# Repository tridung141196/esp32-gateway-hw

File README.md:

# esp32-gateway-hw

## Features

esp32-gateway-hw có thể:
- Điện áp ngõ vào 4 đến 40VDC.

- Sử dụng được nguồn DC, USB, Pin ( có chức năng tự sạc).

- Theo dõi vị trí và trả về thông tin cho người dùng thông qua module GPS Neo6m và module GSM Sim800c.

- Hệ thống đèn báo nguồn , GPS , GSM.

# Nguyên lý hoạt động

- SHield sử dụng module GPS neo6m để định vị tọa độ của thiết bị thông qua hệ thống định vị toàn cầu (GPS) sau đó gửi thông tin toạ độ thiết bị đến người dùng thông qua module sim800c

## Hardware

### Các module đi kèm

ESP32-WROVER-V3

GSM SIM800C

GPS NEO6M

### Schematics

### PCB Layout

### 3D

### Gerber

//[Download](./assets/esp32-cam-shield.zip)

### BOM 

| Designator | Package | Quantity | Designation  |
|---------------------|--------------------------------|----------|-------------------------|
|		      |		                       |	  |	                    |
### Remark

This project was in development phase - we will remove this remark after release

# License

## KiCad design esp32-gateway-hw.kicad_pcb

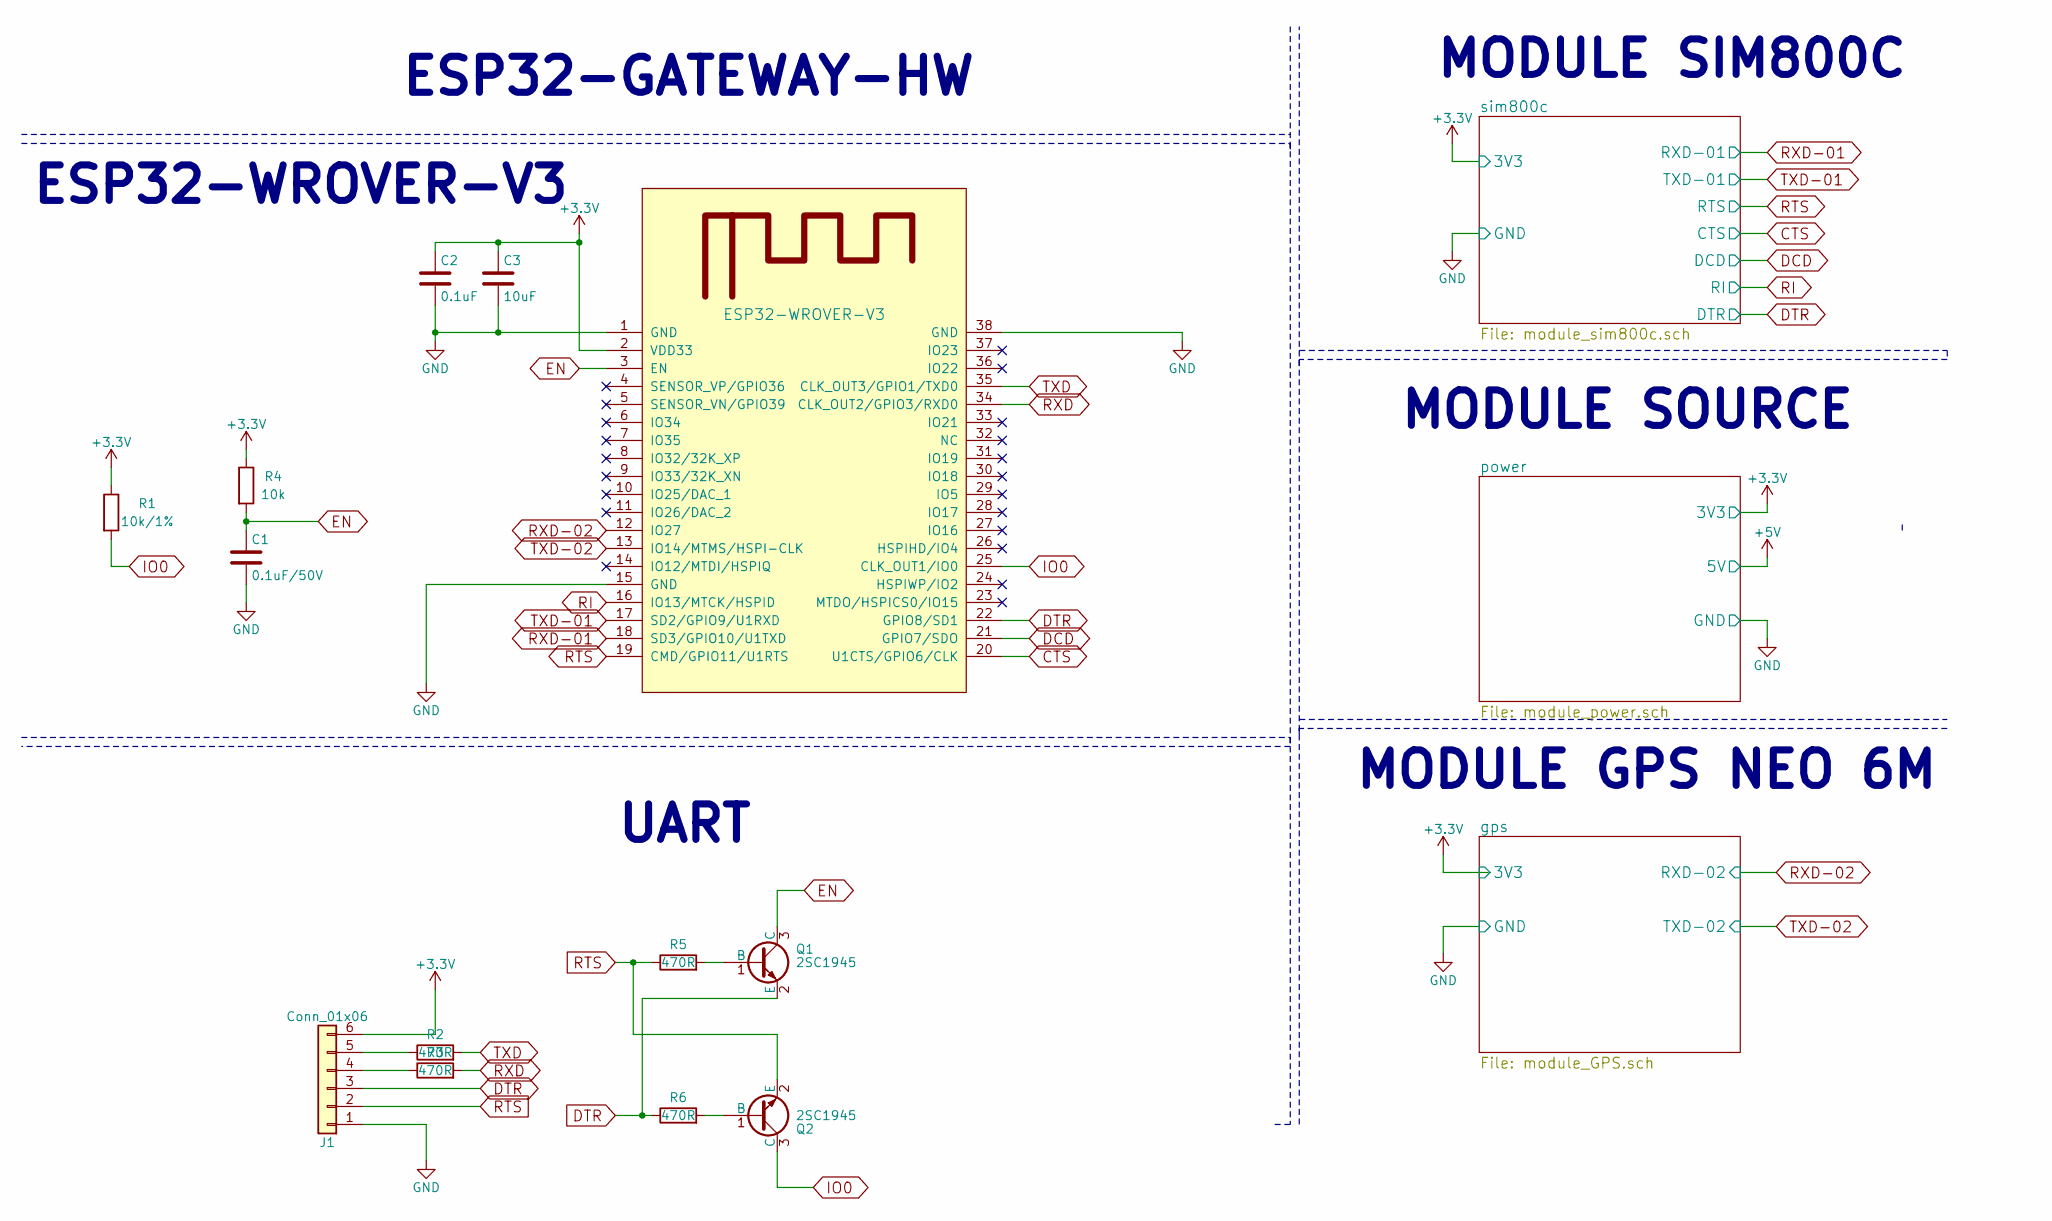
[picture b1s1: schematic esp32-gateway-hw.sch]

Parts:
C1: 0.1uF/50V; C_0603
C2: 0.1uF; C_0603
C3: 10uF; C_0603
J1: Conn_01x06; Pin_Header_Straight_1x06_Pitch2.54mm
Q1, Q2: 2SC1945; SOT-23
R1: 10k/1%; R_0603
R2, R3, R5, R6: 470R; R_0603
R4: 10k; R_0603
U1: ESP32-WROVER-V3; esp32-wrover-32S

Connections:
+3V3: C2.1, C3.1, J1.6, R1.1, R4.1, U1.2 (VDD33); also elsewhere on the board
CTS: U1.20 (U1CTS/GPIO6/CLK); also elsewhere on the board
DCD: U1.21 (GPIO7/SDO); also elsewhere on the board
DTR: J1.3, Q1.2 (E), R6.1, U1.22 (GPIO8/SD1); also elsewhere on the board
EN: C1.1, Q1.3 (C), R4.2, U1.3 (EN)
GND: C1.2, C2.2, C3.2, J1.1, U1.1 (GND), U1.15 (GND), U1.38 (GND); also elsewhere on the board
IO0: Q2.3 (C), R1.2, U1.25 (CLK_OUT1/IO0)
unnamed: J1.4, R3.1
unnamed: J1.5, R2.1
unnamed: Q1.1 (B), R5.2
unnamed: Q2.1 (B), R6.2
RI: U1.16 (IO13/MTCK/HSPID); also elsewhere on the board
RTS: J1.2, Q2.2 (E), R5.1, U1.19 (CMD/GPIO11/U1RTS); also elsewhere on the board
RXD: R3.2, U1.34 (CLK_OUT2/GPIO3/RXD0)
RXD-01: U1.18 (SD3/GPIO10/U1TXD); also elsewhere on the board
RXD-02: U1.12 (IO27); also elsewhere on the board
TXD: R2.2, U1.35 (CLK_OUT3/GPIO1/TXD0)
TXD-01: U1.17 (SD2/GPIO9/U1RXD); also elsewhere on the board
TXD-02: U1.13 (IO14/MTMS/HSPI-CLK); also elsewhere on the board

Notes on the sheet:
ESP32-GATEWAY-HW
MODULE GPS NEO 6M
MODULE SOURCE
MODULE SIM800C
ESP32-WROVER-V3
UART

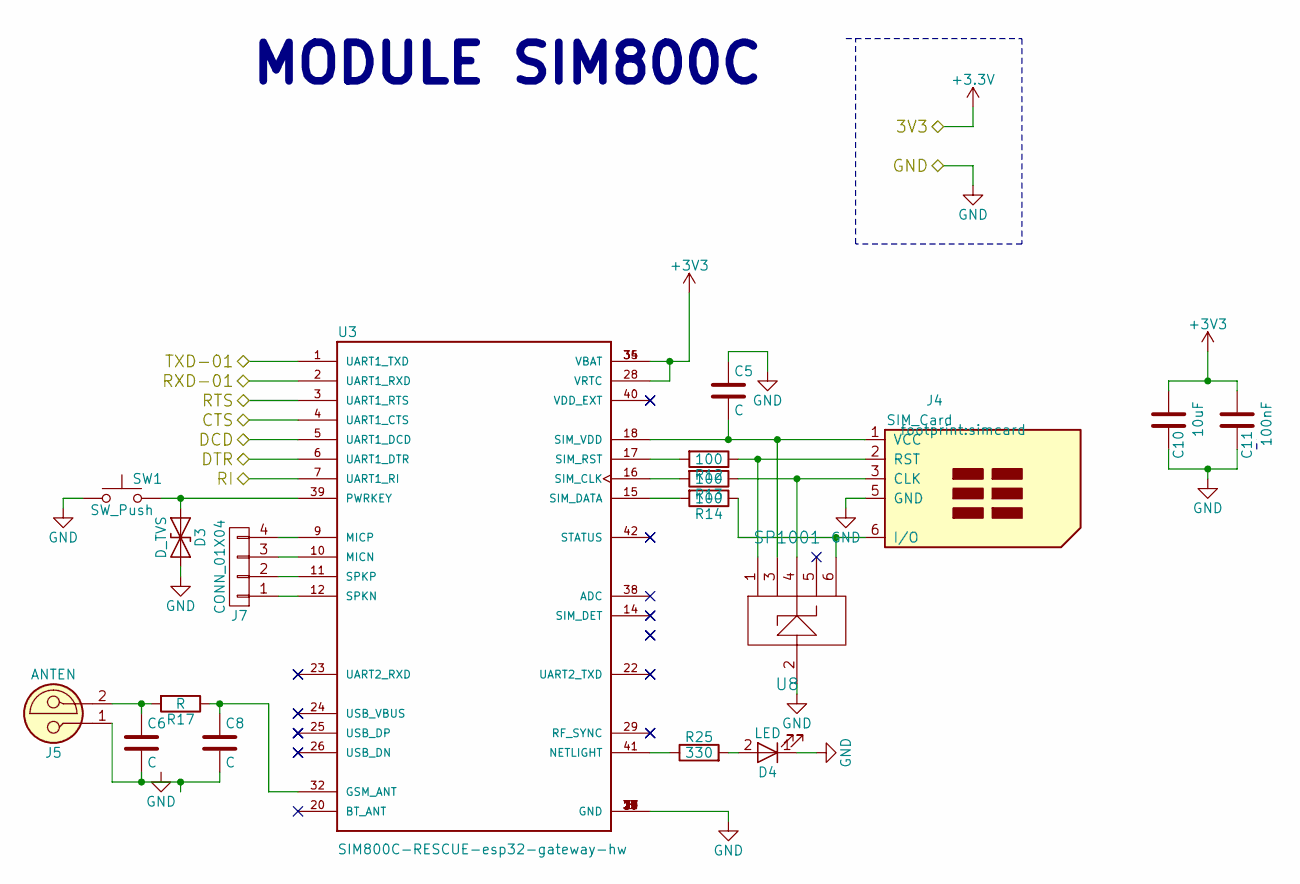
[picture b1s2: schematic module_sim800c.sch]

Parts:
C5, C6, C8: C; C_0603
C10: 10uF; C_0603
C11: 100nF; C_0603
D3: D_TVS; D_1206
D4: LED; LED_D3.0mm
J4: SIM_Card; simcard
J5: ANTEN; SMA_Straight
J7: CONN_01X04; Pin_Header_Straight_1x04_Pitch2.54mm
R12, R13, R14: 100; R_0603
R17: R; R_0603
R25: 330; R_0603
SW1: SW_Push; Tact_Switch_TS6X3.6
U3: SIM800C-RESCUE-esp32-gateway-hw; sim800c
U8: SP1001

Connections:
+3V3: C10.2, C11.2, U3.28 (VRTC), U3.34 (VBAT), U3.35 (VBAT); also elsewhere on the board
CTS: U3.4 (UART1_CTS); also elsewhere on the board
DCD: U3.5 (UART1_DCD); also elsewhere on the board
DTR: U3.6 (UART1_DTR); also elsewhere on the board
GND: C5.1, C10.1, C11.1, D3.2 (A2), D4.1 (K), J4.5 (GND), SW1.1, U3.8 (GND), U3.13 (GND), U3.19 (GND), U3.21 (GND), U3.27 (GND), U3.30 (GND), U3.31 (GND), U3.33 (GND), U3.36 (GND), U3.37 (GND), U8.2; also elsewhere on the board
unnamed: C5.2, J4.1 (VCC), U3.18 (SIM_VDD), U8.3
unnamed: C6.1, J5.2, R17.2
unnamed: C6.2, C8.2, J5.1
unnamed: C8.1, R17.1, U3.32 (GSM_ANT)
unnamed: D3.1 (A1), SW1.2, U3.39 (PWRKEY)
unnamed: D4.2 (A), R25.2
unnamed: J4.2 (RST), R12.1, U8.1
unnamed: J4.3 (CLK), R13.1, U8.4
unnamed: J4.6 (I/O), R14.1, U8.6
unnamed: J7.1, U3.12 (SPKN)
unnamed: J7.2, U3.11 (SPKP)
unnamed: J7.3, U3.10 (MICN)
unnamed: J7.4, U3.9 (MICP)
unnamed: R12.2, U3.17 (SIM_RST)
unnamed: R13.2, U3.16 (SIM_CLK)
unnamed: R14.2, U3.15 (SIM_DATA)
unnamed: R25.1, U3.41 (NETLIGHT)
RI: U3.7 (UART1_RI); also elsewhere on the board
RTS: U3.3 (UART1_RTS); also elsewhere on the board
RXD-01: U3.2 (UART1_RXD); also elsewhere on the board
TXD-01: U3.1 (UART1_TXD); also elsewhere on the board

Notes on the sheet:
MODULE SIM800C

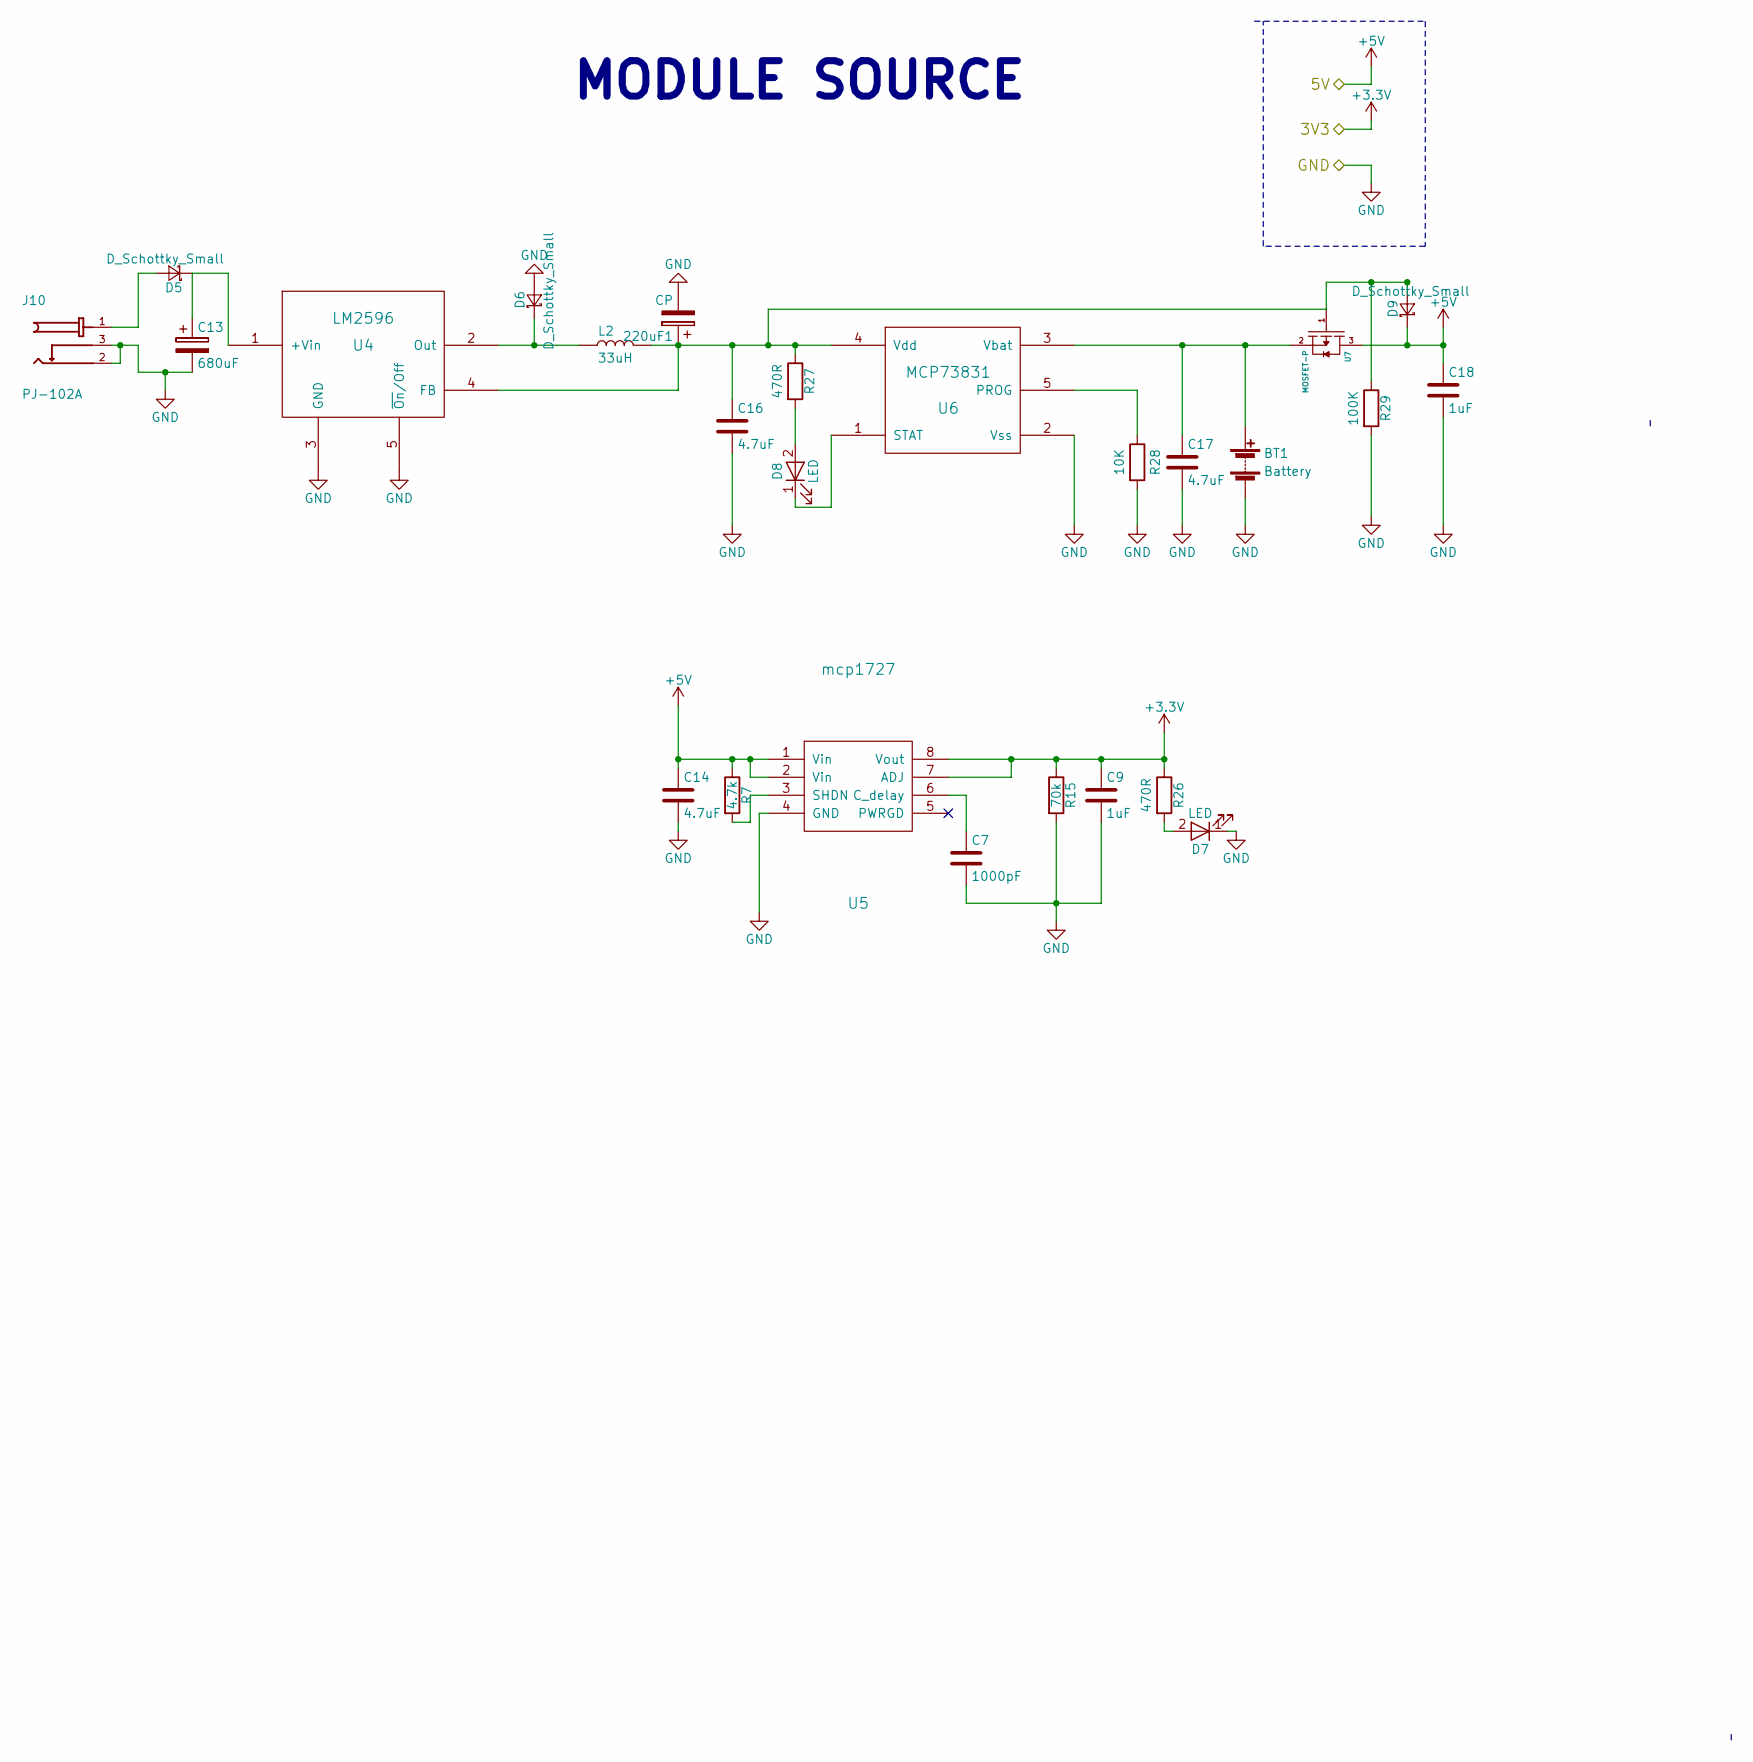
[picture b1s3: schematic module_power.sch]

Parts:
220uF1: CP; CP_Elec_4x4.5
BT1: Battery; Pin_Header_Straight_1x02_Pitch2.54mm
C7: 1000pF; C_0603
C9, C18: 1uF; C_0603
C13: 680uF; CP_Radial_D10.0mm_P5.00mm
C14, C16, C17: 4.7uF; C_0603
D5, D6, D9: D_Schottky_Small; D_SOD-323
D7, D8: LED; LED_D3.0mm
J10: PJ-102A; jackdc
L2: 33uH; L_6.3x6.3_H3
R7: 4.7k; R_0603
R15: 70k; R_0603
R26, R27: 470R; R_0603
R28: 10K; R_0603
R29: 100K; R_0603
U4: LM2596; TO-252-5_TabPin3
U5: mcp1727
U6: MCP73831; SOT-23-5
U7: MOSFET-P; SOT-23_Handsoldering

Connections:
+3V3: C9.1, R15.1, R26.1, U5.7 (ADJ), U5.8 (Vout); also elsewhere on the board
+5V: C14.1, C18.1, D9.1 (K), R7.1, U5.1 (Vin), U5.2 (Vin), U7.3
GND: 220uF1.2, BT1.2 (-), C7.2, C9.2, C13.2, C14.2, C16.2, C17.2, C18.2, D6.2 (A), D7.1 (K), J10.2, J10.3, R15.2, R28.2, R29.2, U4.3 (GND), U4.5 (~On~/Off), U5.4 (GND), U6.2 (Vss); also elsewhere on the board
unnamed: 220uF1.1, C16.1, D9.2 (A), L2.2, R27.1, R29.1, U4.4 (FB), U6.4 (Vdd), U7.1
unnamed: BT1.1 (+), C17.1, U6.3 (Vbat), U7.2
unnamed: C7.1, U5.6 (C_delay)
unnamed: C13.1, D5.1 (K), U4.1 (+Vin)
unnamed: D5.2 (A), J10.1
unnamed: D6.1 (K), L2.1, U4.2 (Out)
unnamed: D7.2 (A), R26.2
unnamed: D8.1 (K), U6.1 (STAT)
unnamed: D8.2 (A), R27.2
unnamed: R7.2, U5.3 (SHDN)
unnamed: R28.1, U6.5 (PROG)

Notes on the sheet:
MODULE SOURCE

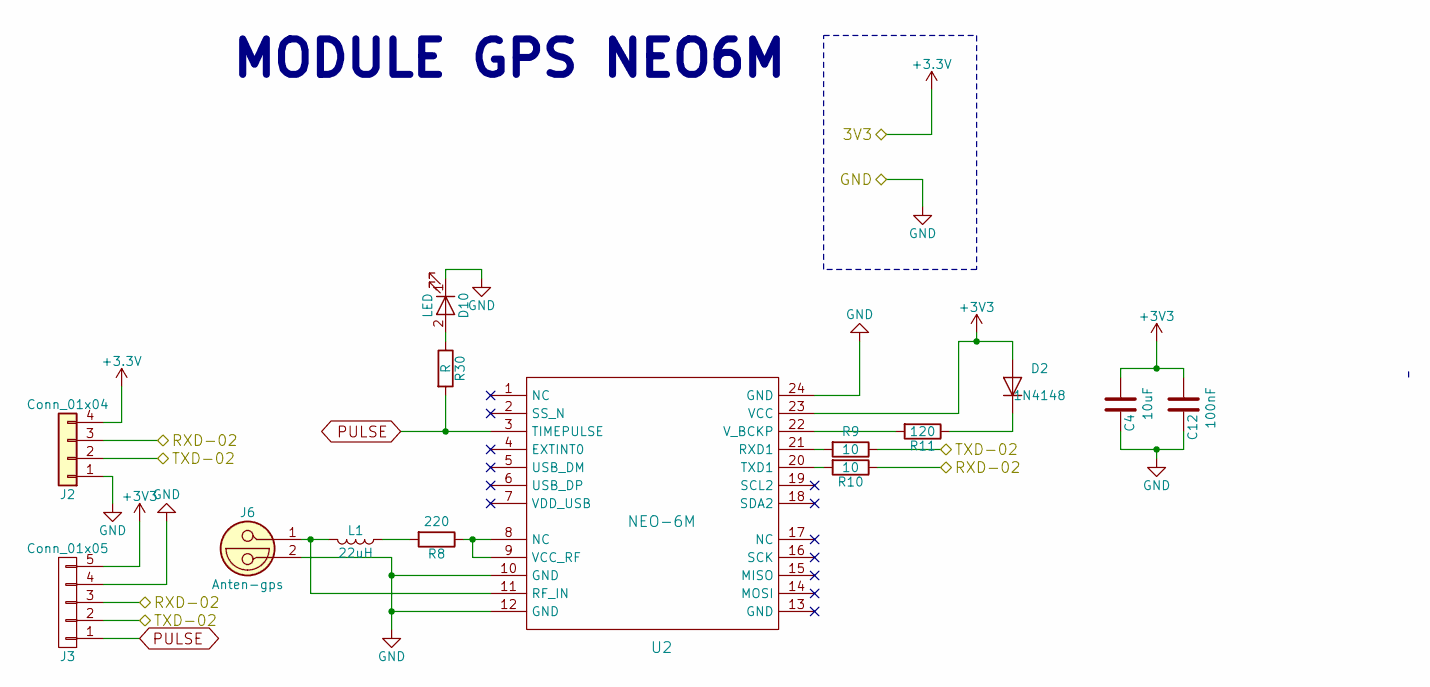
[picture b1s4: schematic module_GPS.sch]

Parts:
C4: 10uF; C_0603
C12: 100nF; C_0603
D2: 1N4148; D_SOD-123
D10: LED; LED_D3.0mm
J2: Conn_01x04; Pin_Header_Straight_1x04_Pitch2.54mm
J3: Conn_01x05; Pin_Header_Straight_1x05_Pitch2.54mm
J6: Anten-gps; SMA_Straight
L1: 22uH; L_1206
R8: 220; R_0603
R9, R10: 10; R_0603
R11: 120; R_0603
R30: R; R_0603
U2: NEO-6M; gps-neo6m

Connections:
+3V3: C4.2, C12.2, D2.2 (A), J2.4, J3.5, U2.23 (VCC); also elsewhere on the board
GND: C4.1, C12.1, D10.1 (K), J2.1, J3.4, J6.2, U2.10 (GND), U2.12 (GND), U2.24 (GND); also elsewhere on the board
unnamed: D2.1 (K), R11.1
unnamed: D10.2 (A), R30.1
unnamed: J6.1, L1.2, U2.11 (RF_IN)
unnamed: L1.1, R8.2
unnamed: R8.1, U2.8 (NC), U2.9 (VCC_RF)
unnamed: R9.2, U2.21 (RXD1)
unnamed: R10.2, U2.20 (TXD1)
unnamed: R11.2, U2.22 (V_BCKP)
PULSE: J3.1, R30.2, U2.3 (TIMEPULSE)
RXD-02: J2.3, J3.3, R10.1; also elsewhere on the board
TXD-02: J2.2, J3.2, R9.1; also elsewhere on the board

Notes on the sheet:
MODULE GPS NEO6M

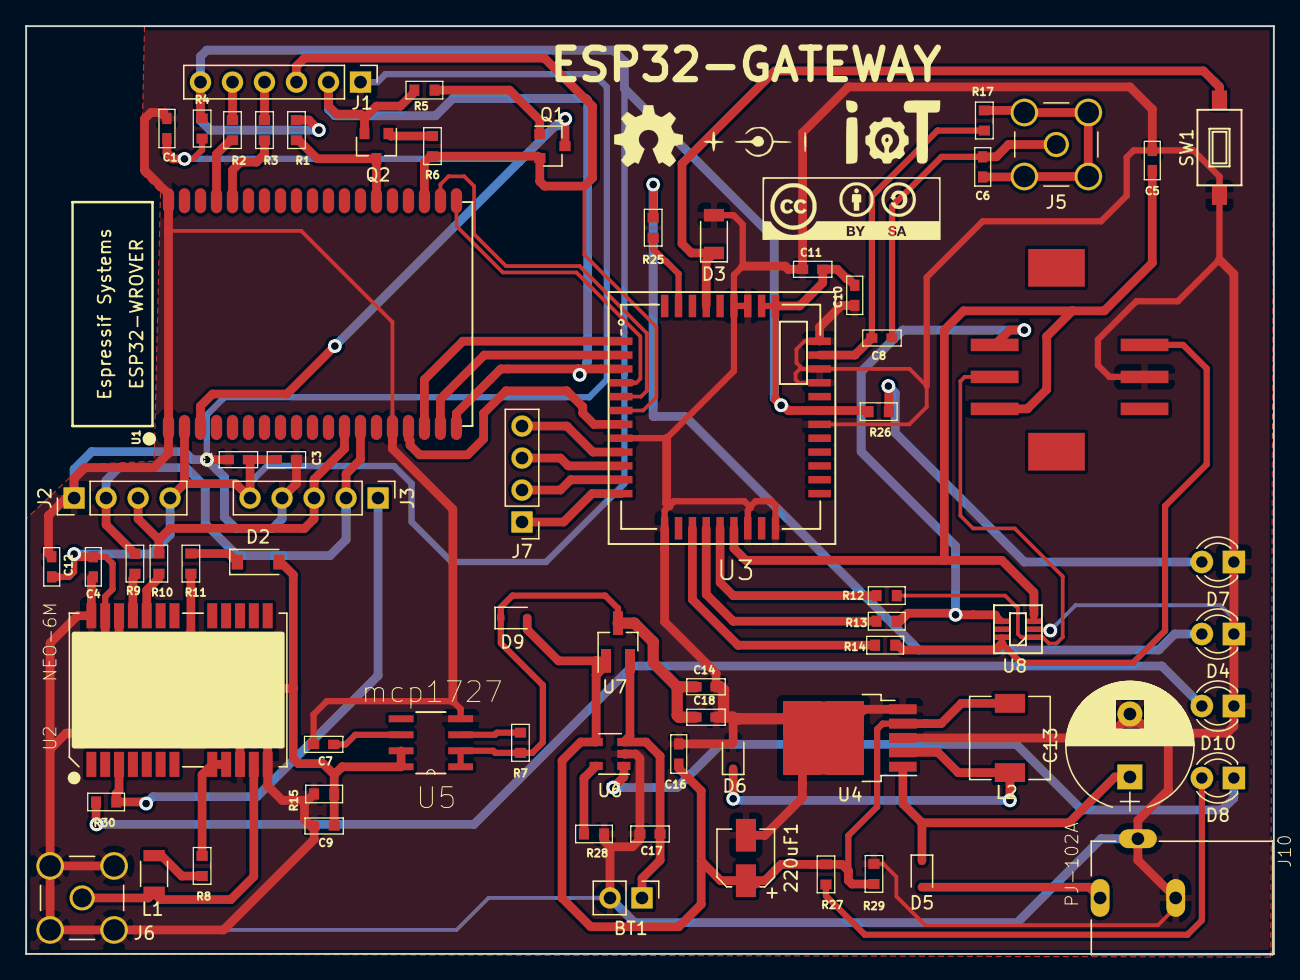
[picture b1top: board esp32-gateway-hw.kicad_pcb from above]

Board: 2 copper layers, 99.1 x 73.7 mm, 71 parts (0 on the bottom side), 57 nets.

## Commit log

2017-10-10 new file module power
2017-10-10 tong hop module
2017-10-10 complete schematic
2017-10-10 fix usb uart
2017-10-10 add footprint neo-6m
2017-10-10 edit module sim800c
2017-10-11 add footprint sim 800
2017-10-11 fix mach nap
2017-10-11 update layout
2017-10-11 edit sheet module
2017-10-11 edit readme
2017-10-11 edit schematic
2017-10-17 add footprint mcp1727
2017-10-18 edit layout
2017-10-18 edit pcd
